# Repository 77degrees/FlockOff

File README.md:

# FlockOff
Wardriving Flock Security camera detection

## Description
This started of strictly as a Flock detector, but grew into more.  In general, it is a device to monitor WiFi and BTLE networks, setting an indicator whenever a broadcaster is found that meets preset parameters.  For WiFi networks, those parameters can be a MAC OID or network name (SSID).  For Bluetooth, the matching critera can be name, MAC, or by specific 16-bit UUIDs.

The hardware device consists of an ESP32-S3 dev board, a serial GPS module, and two LEDs for signalling.

There is a serial interface to the hardware device with a rich CLI (command-line interface).  The device can also be used stand-alone (results are stored to internal file system) or by scripting.

## Project structure
The files contained in the project:
+ `./hardware` - contains a KiCad project for the board
+ `./img` - images used in this README
+ `./py` - simply python3 script to interact with the flocker (notes below)
+ `./src` - source code (arduino project) for the ESP32 (notes below)

### Hardware

The hardware is dead simple - two dev modules, two through-hole 8mm WS2812 LEDs, and a small signal diode:
+ [ESP32-S3](https://www.amazon.com/Dual-core-Supported-Efficiency-Interface-Robotics/dp/B0DJ6NQFKX/ref=sxin_17_pa_sp_search_thematic_sspa?content-id=amzn1.sym.acab9f82-fc77-4a20-9021-7b5c22d80ec5%3Aamzn1.sym.acab9f82-fc77-4a20-9021-7b5c22d80ec5&crid=2JDD3FE6II334&cv_ct_cx=esp32s3&keywords=esp32s3&pd_rd_i=B0DJ6NQFKX&pd_rd_r=111273b0-33b8-492d-943f-a421e25d3cd0&pd_rd_w=tgPcF&pd_rd_wg=AKjP3&pf_rd_p=acab9f82-fc77-4a20-9021-7b5c22d80ec5&pf_rd_r=M8JMDJXXJ54DR9BMEQC6&qid=1765833241&s=electronics&sbo=RZvfv%2F%2FHxDF%2BO5021pAnSA%3D%3D&sprefix=esp32s3%2Celectronics%2C142&sr=1-2-6024b2a3-78e4-4fed-8fed-e1613be3bcce-spons&aref=L2fTwRUg09&sp_csd=d2lkZ2V0TmFtZT1zcF9zZWFyY2hfdGhlbWF0aWM&th=1) I picked this module because of small size, good price, and 8MB of both flash and PSRAM
+ [GPS Module](https://www.amazon.com/hiBCTR-Navigation-Positioning-Microcontroller-Sensitivity/dp/B0FL71WTQY/ref=sr_1_2?crid=2EM3EOXRCSTFT&dib=eyJ2IjoiMSJ9.XRWR-WnPLsz7cVN0GpjqJTxFRMO10MBskzPEVvz5LCTDXAtxa_rXf2wQrFndRzU50l7y__POWiiDMUXVK5OIa7VqEst8IqFH4xFvcnBHg-U0VY4qNZQPKFdzWL5Evdyj4AFWD0VpzcrnOxwnca7-Dr8wspdKucj2aYc0Gtoa1uRUl7K4ES9h20ztgmGDT3mPrt2tiQ-HN-FAgOPFQVPE3Pudl5vF2LNCPSp00W8Bhg5xvlYpIlCSGdX8GwmWiVH8u0OJW8YW5ridkpLchugFbq4H7w5SYdWBFkT73FZqAvk.YyvKMYAZdg815_BV_j8Fv4HH-0O0dOLUrndqKjRR0CQ&dib_tag=se&keywords=4+Pack+GPS+Module%2C+NEO-6M+Navigation+Positioning%2C+Arduino+GPS+for+Drone+Microcontroller%2C+High+Sensitivity+Receiver+with+Antenna%2C+Compatible+with+51+Microcontroller+STM32+Arduino+UNO+R3&nsdOptOutParam=true&qid=1765833097&s=electronics&sprefix=4+pack+gps+module%2C+neo-6m+navigation+positioning%2C+arduino+gps+for+drone+microcontroller%2C+high+sensitivity+receiver+with+antenna%2C+compatible+with+51+microcontroller+stm32+arduino+uno+r3%2Celectronics%2C158&sr=1-2) There is notthing special about this particular module; it is a basic GPS with NMEA serial interface, it was cheap, and in stock at Amazon
+ [WS1812 LEDs](https://www.adafruit.com/product/1734)  These are interesting in that they are the typical addressable LEDs, but in a through-hole 8mm package.  They are great for using as signalling/status indicators.  Also handy because there are so many libraries to work with them.
+ [1N4148 Diode](amazon.com/ALLECIN-1N4148-Schottky-Switching-Package/dp/B0CKRMK45V/ref=sr_1_6_sspa?dib=eyJ2IjoiMSJ9.5f18Rx_7lMSBN-40Nk5_scirzd5gVqG_sr48GsP-pxJ7RyARr5GHbm76WgpJle4ywCwcEGfv6m5ZR-PIBoBmRN28qtEe29DQYY84c263_q6oFDujaGGVK8-qabhrRd_IZtu2PwFHkKMBdiIw8IDQjSYkBxPm9DKi_AA6exCA7rmOiWGNdN9Oq0D-5c1H1XGK1kBii_ftCc-F3YiORaBovQ5vkFW9kAN3zzAu7IgDKEk.RF6rc4KmtAVvY9uUuLV-Zf6xt-HBLaOGQf1vvRW5V2U&dib_tag=se&keywords=1n4148&qid=1765833550&sr=8-6-spons&sp_csd=d2lkZ2V0TmFtZT1zcF9tdGY&psc=1) (Amazon link for reference, I had some in my parts bin).  This is used because it has a forward voltage drop of about .7V.

#### What's up with the diode?

Like pretty much all WS2812 LEDs, these need 5VDC to operate; 5VDC power, 5VDC data line.  The ESP32 is a 3.3 microcontroller, so what to do?

The USB connection supplies 5V which is regulated down to 3.3V for the microcontroller and associated stuff.  In the schematic above, `D3` is shown between the 5V USB power and the LED power in pin; that drops the voltage to about 4.3VDC.  That's just within spec for the LED, and it is still plenty bright.

The 3.3V signal data line from the ESP32 would be too low if the LED was powered by 5V, but is just enough with the LED at 4.3-ish.  It's a cheat to get away without having to use level converters; not something I'd do for a "real" production project, but good enough for here.

### Firmware
The firmware is written using the Arduino IDE.  In the past, I've always avoided that and used VS Code with my own Makefile or CMAKE, PlatformIO, or whatever.  I decided to go with Arduino in this case because I'm very unhappy with the integration of Copilot into VS Code (and really, the push to shove AI into everything).  For now, Ardiuno is just code.

The libraries needed for this project are:
+ ArduinoJson (7.4.2) - for JSON, obviously
+ EspSoftwareSerial (8.1.0) - for the software UART to the GPS module
+ LiteLED (3.0.1) - for the two addressable LEDs
+ NimBLE-Arduino - for the BLE detection stuff

Of course, the core ESP32 stuff needs to be installed (I'm using the Espressif ESP32 board package, v3.3.3).

In addition, the board configuration is:
+ Board: `ESP32S3 Dev Module`
+ USB CDC on Boot: `Enabled`
+ Flash Mode: `QIO 80MHz`
+ Flash Size: `8MB`
+ Partition Scheme: `Custom` - see `./src/partitions.csv`, but basically 3MB application, 4MB filesystem
+ PSRAM: `OPI PSRAM`
I believe everything else is default.

### CLI Interface
There is a CLI available at the USB port at 115200/8N1.  The CLI uses ANSII escape codes for color, has tab-completion, up-arrow recall, and help:
```  
Flock Off $>help 
Use 'command -h' for detailed help on each command
	help - Print list of commands
	survey - Perform Wifi survey
	clear - Clear the console
	reset - Reboot the device
	ls - List files
	rm - Delete file
	write - Write test file
	mv - Rename file
	cp - Copy file
	cat - Cat file
	status - Get system status
	config - Get/Set config values
```  
Passing a `-h` to any command will show help for that command, for example:
```  
Flock Off $>survey -h
survey [OPTION]
Perform a WiFi and/or Bluetooth survey.  Displays all results, not just those that match scan criteria.

  -i <INTERVAL>   interval in milliseconds to scan each WiFi channel
  -w              scan WiFi for broadcasters
  -b              scan for Bluetooth broadcasters
  -f <FILENAME>   save results to FILENAME
  -j <NOTES>      save results as JSON, with NOTES added for reference

If neither the -b or -w parameter is set, a survey of both will be performed.  If data is saved to file, but the -j parameter is not supplied, the data will be in CSV format.
```  
There is a flat filesystem included (flat, meaning no directories; all files are in a single directory). Basic Linux-type file management commands are available, but note that there is no 'globbing'; all filenames must be directly entered.  Examples:
```  
Flock Off $>ls 
	   208  config.bak
	   207  config.json
	   306  survey.00.json
	  3840  survey.01.json
	   408  system.log
Flock Off $>cat config.json
{"deviceName":"SuperSecret Sniffer","timeZone":"CST6CDT,M3.2.0,M11.1.0","LEDBrightness":128,"debugEnabled":true,"debugLogRollCount":3,"minRSSI":-85,"WifiAPs":["flock","fs ext Battery","penguin","pigvision"]}
```  
Configuration is menu-driven:
```  
Flock Off $>config 
1) Set device name (SuperSecret Sniffer)
2) Set timezone (CST6CDT,M3.2.0,M11.1.0)
3) Set max LED brightness (128)
4) Set debug logging (enabled)
5) Set debug file rolling count (3)
6) Set minimum RSSI (-85)
Select number of item to change or 'x' to exit with no changes: 
```  
## LEDs
What do the LEDs do?
### GPS LED
| color | description |  
|---|---|  
| Green blink | GPS Fix good, communication good |  
| Purple blink | GPS no fix, communication good |  
| Red blink | No comms to GPS module |  

### RF LED
| color | description |  
|---|---|  
| Blue fade alert | Survey in progress | 
| Red fade alert | Target device in range |  

## Performing a site survey
A survey will report all WiFi and BTLE broadcasters in range.  Why perform a survey?  Maybe there's a known device that isn't triggering alerts, and we want to characterize it (find MAC address, if BT, see if there are any service UUIDs it's broadcasting).

Basic steps:
1) Connect to the device with a serial terminal of your choice (PuTTY on Windows, TIO/minicom oon Linux, whatever on MAC).
2) Use the `status` command to be sure GPS has gotten a fix and that the data looks correct (GPS coordinates masked by me for privacy):
``` 
Flock Off $>status 
->GPS:
	GPS current coordinates are 42.XXXXX, -87.XXXXX
	GPS current time/date (gmt) is 21:51:54 11/15/2025
	Number of satellites currently tracked: 7
->Filesystem:
	Total capacity 4194304 bytes, 16384 used (4080 KiB free)
->Memories:
	Internal total heap 325156 bytes, 88340 used (231 KiB free)
	PSRAM total heap 8388608 bytes, 24688 used (8192 KiB free)
->Wall clock:
	Current wall clock time is Mon, 15 Dec 2025 15:51:54 -0600
	Timezone is set to CST6CDT,M3.2.0,M11.1.0
```  
3) Use the `survey` command to start the survey.  Parameters are:
   + `-i INTERVAL` defines how much time (milliseconds) to spend on each WiFi channel
   + `-w` for WiFi only, `-b` for BTLE only (or neither for both)
   + `-j NOTES` to save the results in a JSON file, with survey notes set to `NOTES`
   + `-f FILENAME` to save results
```  
Flock Off $>survey -i 2000 -j 'Example survey' -f survey.example.json
Survey starting.
Starting WiFi.
Setting channel 1...2...3...4...5...6...7...8...9...10...11...12...13...36...40...44...48...149...153...157...161...165
WiFi done.
Starting BLE
SCANNER::stopBLE() - scanner was non-null
BLE Done, survey complete, found 21 devices
Found 33 devices:

Saving survey results to survey.example.json, format JSON
Wrote 4371 bytes to file
```  
This example survey found 12 WiFi devices (or channels on devices), and 21 BTLE devices.  The data in the JSON file looks like this (truncated): 
```
Flock Off $>cat survey.example.json
{"SurveyNotes":"'Example","LocationLongLat":[-87.94199,42.8945],"SatelliteCount":8,"DateTime":"2025-12-15 15:56:52","Timezone":"CST6CDT,M3.2.0,M11.1.0","WiFiDevices":[{"Method":"WiFi","Subtype":"beacon","BSSID":"b2:28:aa:1c:0a:29","Channel":2,"SSID":"flu","RSSSI":-51},{"Method":"WiFi","Subtype":"beacon","BSSID":"b2:28:aa:1c:0a:2a","Channel":1,"SSID":"flu_IoT","RSSSI":-52},{"Method":"WiFi","Subtype":"beacon","BSSID":"b2:28:aa:1c:0a:2a","Channel":2,"SSID":"flu_IoT","RSSSI":-53},{"Method":"WiFi","Subtype":"probe response","BSSID":"b2:28:aa:1c:0a:2a","Channel":2,"SSID":"flu_IoT","RSSSI":-54},{"Method":"WiFi","Subtype":"beacon","BSSID":"a0:36:bc:db:ca:a0","Channel":12,"SSID":"virus","RSSSI":-52},
```  
### Interpreting survey results
The included python scripts can pull the survey data from the device and populate some database tables (sqlite3) for analysis.

To do this, start by going to the `./py` directory and running the script.  There are some Python modules needed; they can be installed with the included requirements file (`pip3 install -r requirements.txt`)

*Note - it is always recommended to use a virtual environment with python scripts that require different modules.  See python documentation on how to create and use a virtual environment if necessary.*

Start by listing the files on the device (make sure you are no longer connected to it by serial terminal):
```  
┌──(venv)─(matty💊s76)-[~/data/projects/FlockOff/py]
└─$ python3 ./flock.py --dbfile example.db --port /dev/ttyACM0 --dir                
config.bak
config.json
survey.00.json
survey.01.json
survey.example.json
system.log
```  
The parameters to the `flock.py` script are:
+ `--port PORT` - the serial port of the connected device
+ `--dbfile FILE` - name of the database file to use (it will be created if it does not exist)
+ Command - this is one of a few commands:
  + `--dir` - list the files on the device
  + `--cat FILE` - list the contents of the specified file
  + `--load FILE` - load the specified JSON file into database tables

The above `--dir` comamnd showed our `survey.example.json` from the survey.  Let's load it into the database tables:
```  
┌──(venv)─(matty💊s76)-[~/data/projects/FlockOff/py]
└─$ python3 ./flock.py --dbfile example.db --port /dev/ttyACM0 --load survey.example.json
Loaded 12 WiFi devices, 21 BTLE devices from survey "'Example" at 2025-12-15 15:56:52
```  
### Survey database

The database schema can be seen in `./src/py/survey.db.schema`

The sqlite3 database can be explored with a gui tool or the command line.  The `surveys` table shows basic information about the a survey json file (using `sqlite3` command line tool):
```  
sqlite> .mode box
sqlite> .headers on
sqlite> select * from surveys;
┌───────────┬──────────┬─────────────────────┬───────────┬───────────┬──────────┐
│ surveyInx │  notes   │      dateTime       │ longitude │ lattitude │ satCount │
├───────────┼──────────┼─────────────────────┼───────────┼───────────┼──────────┤
│ 1         │ 'Example │ 2025-12-15 15:56:52 │ 42.0001   │ -87.0001  │ 8        │
└───────────┴──────────┴─────────────────────┴───────────┴───────────┴──────────┘
```  
 The `surveyInx` field is a foreign key into the `wifi` and `btle` tables.  This allows multiple surveys to be loaded into a single database file

`notes` is the value from the `-j NOTES` parameter of the `survey` command.  `dateTime`, `longitude`, `lattitude`, and `satCount` are populated by the GPS module.

The `wifi` table contains discovered broadcasters.  To list all of that data for this survey:
```  
sqlite> select w.type, w.ssid, w.bssid, w.rssi, w.channel from wifi as w join surveys s on w.surveyInx = s.surveyInx where w.type not like 'probe request' order by w.bssid;
┌────────────────┬──────────┬───────────────────┬──────┬─────────┐
│      type      │   ssid   │       bssid       │ rssi │ channel │
├────────────────┼──────────┼───────────────────┼──────┼─────────┤
│ beacon         │ virus    │ a0:36:bc:db:ca:a0 │ -52  │ 12      │
│ beacon         │ virus    │ a0:36:bc:db:ca:a0 │ -51  │ 11      │
│ beacon         │ flu      │ b2:28:aa:1c:0a:29 │ -51  │ 2       │
│ beacon         │ flu      │ b2:28:aa:1c:0a:29 │ -53  │ 1       │
│ probe response │ flu      │ b2:28:aa:1c:0a:29 │ -53  │ 2       │
│ beacon         │ flu_IoT  │ b2:28:aa:1c:0a:2a │ -52  │ 1       │
│ beacon         │ flu_IoT  │ b2:28:aa:1c:0a:2a │ -53  │ 2       │
│ probe response │ flu_IoT  │ b2:28:aa:1c:0a:2a │ -54  │ 2       │
│ beacon         │ <HIDDEN> │ cc:28:aa:1c:0a:28 │ -53  │ 2       │
│ beacon         │ <HIDDEN> │ cc:28:aa:1c:0a:28 │ -51  │ 1       │
└────────────────┴──────────┴───────────────────┴──────┴─────────┘
```  
`type` is the type of 802.11 wifi management packet was captured (beacon, probe request, probe response, etc.), `ssid` is the broadcast ssid, `bssid` is the MAC of the broadcaster, `rssi` is signal strength, and `channel` is the wifi channel.

In this case, there were 3 unique MAC addresses seen, all of relatively the same signal strength.

The `btle` table contains bluetooth broadcasters:
```  
sqlite> select b.name, b.mac, b.rssi from btle as b join surveys s on b.surveyInx = s.surveyInx order by b.mac;
┌───────────────────────┬───────────────────┬──────┐
│         name          │        mac        │ rssi │
├───────────────────────┼───────────────────┼──────┤
│                       │ 01:c5:61:6d:2c:b4 │ -53  │
│                       │ 04:a0:29:10:68:e4 │ -78  │
│                       │ 08:66:98:f2:a3:ba │ -84  │
│                       │ 34:fe:3e:a1:f5:e2 │ -63  │
│                       │ 56:f6:b3:ad:60:5f │ -82  │
│                       │ 66:7f:66:1d:ec:ce │ -68  │
│                       │ 6d:67:db:fd:9e:67 │ -84  │
│                       │ 6e:d3:64:c3:af:77 │ -79  │
│                       │ 77:50:8c:84:fa:72 │ -45  │
│                       │ 78:90:0b:c0:26:1b │ -69  │
│                       │ 7e:91:43:7c:ff:bf │ -75  │
│ OfficeJet 5200 series │ 86:a9:3e:bc:5c:c9 │ -76  │
│                       │ 8c:ea:48:a7:2c:03 │ -73  │
│                       │ a8:51:ab:c6:11:25 │ -82  │
│                       │ c0:c9:9b:f2:d7:43 │ -75  │
│                       │ c1:cf:e2:c9:64:5f │ -85  │
│                       │ ca:ba:59:12:f6:0d │ -66  │
│ N00DM                 │ ce:a3:ad:95:04:29 │ -80  │
│                       │ d5:93:9d:03:9f:f5 │ -80  │
│                       │ ea:a8:d0:6f:67:89 │ -84  │
│                       │ ec:9d:4d:3c:28:2b │ -68  │
└───────────────────────┴───────────────────┴──────┘
```  
There are quite a few BTLE devices found.  To narrow it down to those that are broadcasting a UUID:
```  
sqlite> select b.name, b.mac, u.uuid16 from btle b join uuid16 u on b.btInx = u.btInx where b.surveyInx = 1 order by b.mac;
┌───────────────────────┬───────────────────┬────────┐
│         name          │        mac        │ uuid16 │
├───────────────────────┼───────────────────┼────────┤
│ OfficeJet 5200 series │ 86:a9:3e:bc:5c:c9 │ 65144  │
│ N00DM                 │ ce:a3:ad:95:04:29 │ 65199  │
└───────────────────────┴───────────────────┴────────┘
```

**More SQL examples can be found in `./example.sql`**

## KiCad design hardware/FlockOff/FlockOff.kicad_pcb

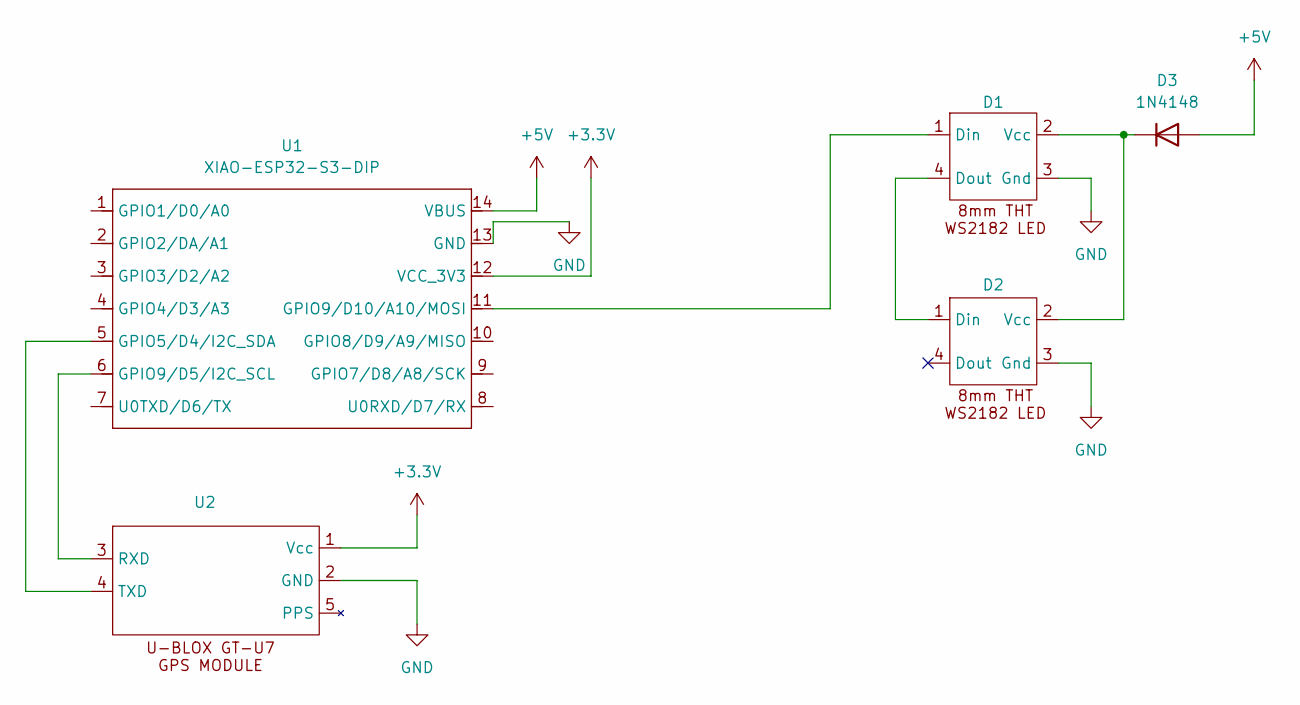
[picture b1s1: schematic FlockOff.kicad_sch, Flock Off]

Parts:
D1, D2: LED_D8.0mm_WS2812
D3: 1N4148; D_DO-35_SOD27_P7.62mm_Horizontal
U1: XIAO-ESP32-S3-DIP; MOUDLE14P-XIAO-DIP-SMD
U2: GPS_Module

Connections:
+3.3V: U1.12 (VCC_3V3), U2.1 (Vcc)
+5V: D3.2 (A), U1.14 (VBUS)
GND: D1.3 (Gnd), D2.3 (Gnd), U1.13 (GND), U2.2 (GND)
unnamed: D1.1 (Din), U1.11 (GPIO9/D10/A10/MOSI)
unnamed: D1.4 (Dout), D2.1 (Din)
unnamed: D1.2 (Vcc), D2.2 (Vcc), D3.1 (K)
unnamed: U1.5 (GPIO5/D4/I2C_SDA), U2.4 (TXD)
unnamed: U1.6 (GPIO9/D5/I2C_SCL), U2.3 (RXD)

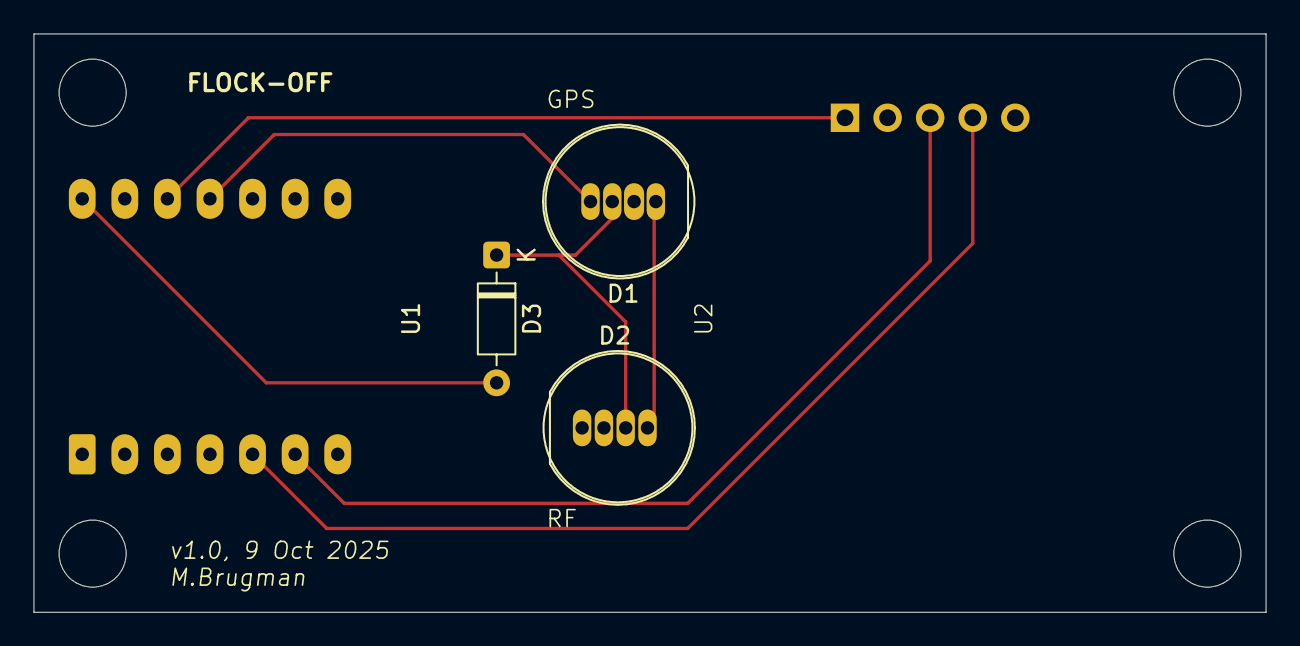
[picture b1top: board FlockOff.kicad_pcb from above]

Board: 2 copper layers, 73.5 x 34.5 mm, 5 parts (0 on the bottom side), 8 nets.

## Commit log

2025-11-14 adding CLI and some hardware stuff
2025-11-17 Adding more cli, cleanup main, adding config json stuffs
2025-11-19 Adding WiFi scanning
2025-11-19 ope, a little cleanup and comments
2025-11-20 using hasher from esp32 core
2025-11-20 starting kunga refactoring. Adding custom partition scheme. Arduino IDE sucks for refactoring - where's the 'clean' function (like make clean)???
2025-11-20 moar refactoring
2025-11-20 refactoring
2025-11-22 rework of wifi detection to actually be logical; starting to replace naked arrays with STL containers where it makes sense.
2025-11-25 survey to JSON and save to file; more cleanup/documentation
2025-11-30 adding bluetooth, inital stuffs
2025-11-30 Moving from proto to first version hardware, including addressible LEDS
2025-11-30 Fix pads for LEDs
2025-12-07 reworking config, start of debug logging, fixup PCB a bit
2025-12-10 adding logging
2025-12-10 moar logging
2025-12-11 actual bluetooth analysis/capture stuff started
2025-12-12 good data gathering from BTLE
2025-12-12 starting python stuffs
2025-12-14 direct load to sqlite3
2025-12-15 clean up in python, clean up CLI help, added min RSSI setting, added -d to cat and ls
2025-12-15 starting on README
2025-12-15 ope, forgot to save README before push
2025-12-17 fix logger timing issue. Added known assigned numbers from bluetooth org to python database driver
2025-12-17 adding MAC lookup
2026-01-04 adding dev instructions, fixing python scripts for mac python3
2026-01-04 added unsaved completion of dev.md
2026-01-04 adding start of 3d printed case model
2026-01-07 working on case
2026-01-07 Add 'download' command to python script to locally save json files
2026-01-07 moar case work. ugh.
2026-01-07 first draft of (ugly) case done, ready to test print
2026-01-07 add a bit to developing.md
2026-01-08 Updated case. Tres fancy! :D
2026-01-09 Moar case (#4)
    * Adding lanyard ring to case, re-rendering .stl files
    * new docs
2026-01-10 added 1mm to top to better handle counterbore of 3mm SHCS
2026-01-10 documenting
2026-01-10 some docs
2026-01-10 ope, forgot to MarkDown like an image
2026-01-10 Moar case (#6)
    * Adding lanyard ring to case, re-rendering .stl files
    * new docs
    * added 1mm to top to better handle counterbore of 3mm SHCS
    * some docs
    * ope, forgot to MarkDown like an image
    * documenting
2026-01-11 Fixed bt scan memory leak (#7)
2026-01-12 Fix scanner bugs (#8)
    * Fixed bt scan memory leak
    * cleaning up some cruft
2026-01-13 fix allocation/free, docs docs docs (#11)
2026-01-13 Develop (#12)
    * fix allocation/free, docs docs docs
    * Missed a file in docs
2026-01-14 Merge added WiFi functionality into main (#14)
    * fix allocation/free, docs docs docs
    * Missed a file in docs
    * Add more wifi packets (#13)
    * Adding general data WiFI packets
    * Adding WiFi data packet gathering, major (breaking) database and python changes
2026-01-15 Added 'version' command, changed database schema to add device name to surveys table, updated scanner to tweak BT duration. Changes to example sql and python script to go with DB schema changes. (#15)
2026-01-17 Increase survey buffer size (due to more wifi devices found). Update ls command to show file last modified data/time
2026-01-19 Starting scan cmd (#17)
    * starting framework for scan command, added config values, adding scan update method
    * continuous scan and autoscan in place; needs filtering
2026-01-21 Add match criteria (#18)
    * beginning to add match criteria handler
    * Added new Allocator class for STL types to go into PS_RAM instead of SRAM, added python script to get OUIs from json, add matching stuff
2026-01-21 Add match criteria (#19)
    * beginning to add match criteria handler
    * Added new Allocator class for STL types to go into PS_RAM instead of SRAM, added python script to get OUIs from json, add matching stuff
    * Missed this file in last PR
2026-01-21 updated header image, copyright date; corrected reversed lat/long (#20)
2026-01-23 cleaning up flk namespace, updates to README (#21)
2026-02-03 clean up logging and messaging around wifi matching, added default wifi ssid matching (#23)
2026-02-11 Add 32bit uuids, db schema update, bug fixes (#24)
    * Adding UUID32 size BT data and service
    * Updating sample SQL queries and fixing bug with python
